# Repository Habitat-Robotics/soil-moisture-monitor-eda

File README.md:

# soil-moisture-monitor-eda
PCB design for soil moisture monitoring circuit
# added circular pcb

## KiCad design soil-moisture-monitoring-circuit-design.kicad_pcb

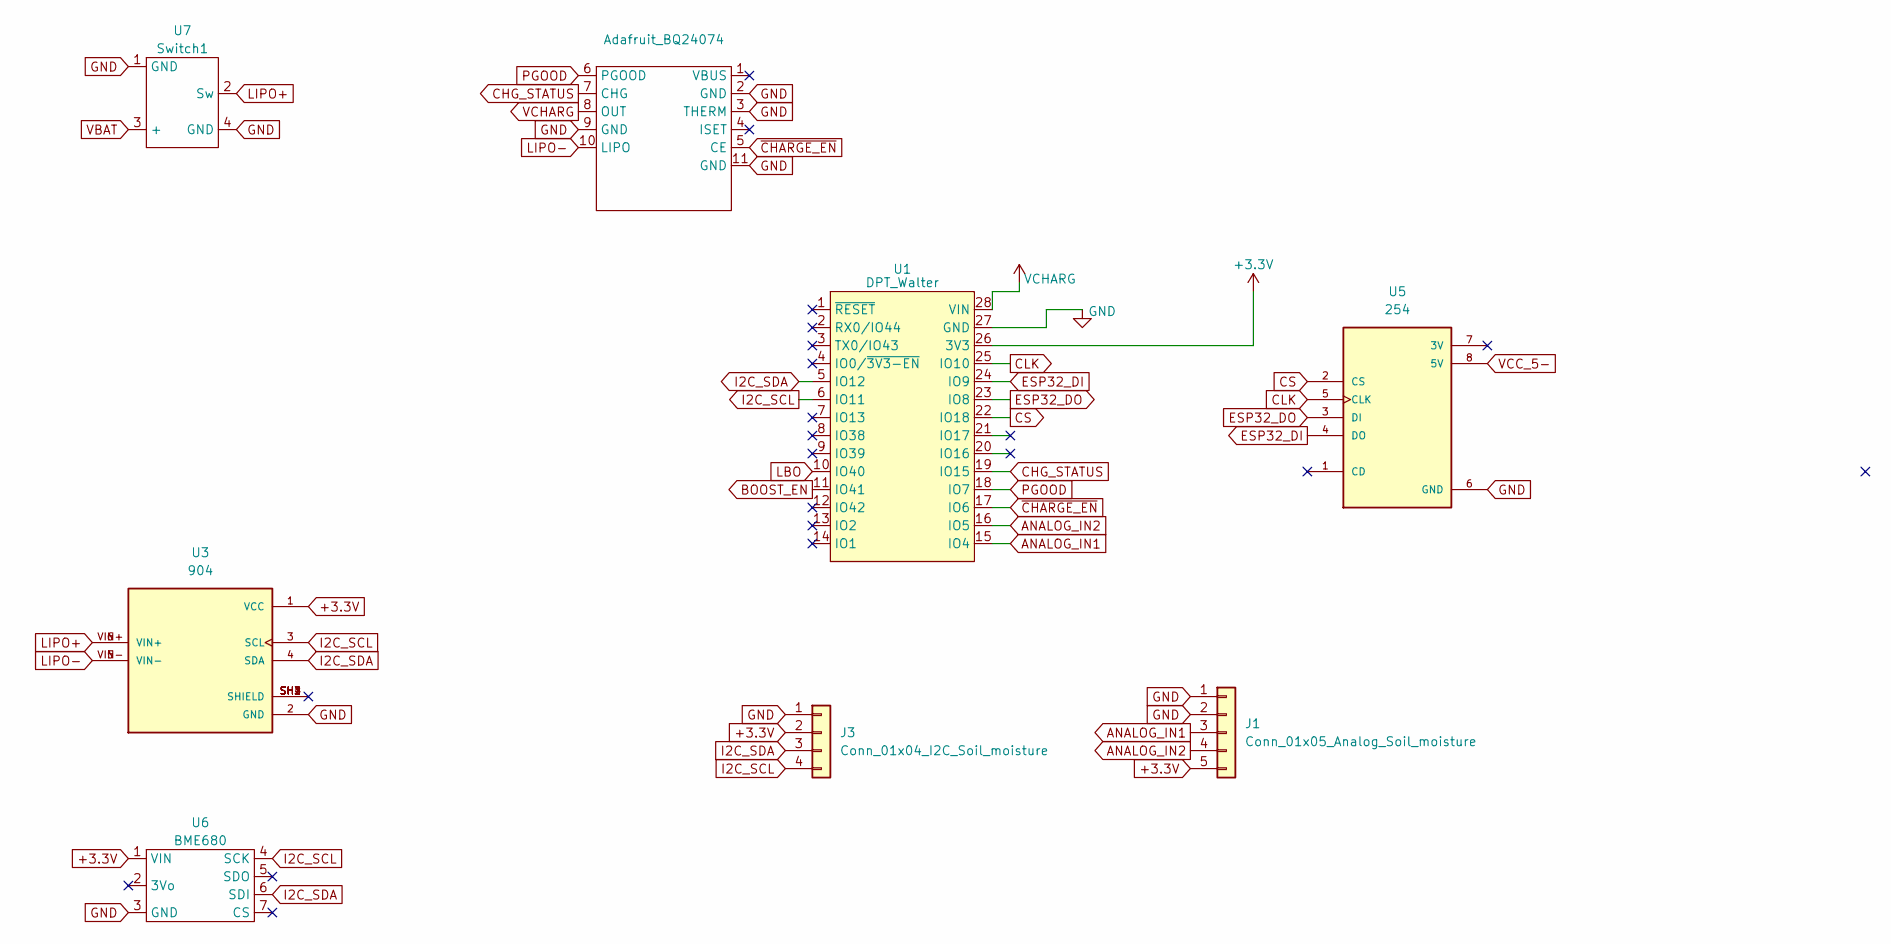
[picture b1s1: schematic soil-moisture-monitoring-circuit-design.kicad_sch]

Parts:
Adafruit_BQ24074: Adafruit_BQ24074
J1: Conn_01x05_Analog_Soil_moisture; PinHeader_1x05_P2.54mm_Vertical
J3: Conn_01x04_I2C_Soil_moisture; PinHeader_1x04_P2.00mm_Vertical
U1: DPT_Walter; walter-solder
U3: 904; MODULE_904; PARTREV C
U5: 254; MODULE_254; PARTREV Jul 31, 2013
U6: BME680; Adafruit_BME680_throughole
U7: Switch1

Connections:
+3.3V: J1.5, J3.2, U1.26 (3V3), U3.1 (VCC), U6.1 (VIN)
ANALOG_IN1: J1.3, U1.15 (IO4)
ANALOG_IN2: J1.4, U1.16 (IO5)
BOOST_EN: U1.11 (IO41)
CHG_STATUS: Adafruit_BQ24074.7 (CHG), U1.19 (IO15)
CLK: U1.25 (IO10), U5.5 (CLK)
CS: U1.22 (IO18), U5.2 (CS)
ESP32_DI: U1.24 (IO9), U5.4 (DO)
ESP32_DO: U1.23 (IO8), U5.3 (DI)
GND: Adafruit_BQ24074.2 (GND), Adafruit_BQ24074.3 (THERM), Adafruit_BQ24074.9 (GND), Adafruit_BQ24074.11 (GND), J1.1, J1.2, J3.1, U1.27 (GND), U3.2 (GND), U5.6 (GND), U6.3 (GND), U7.1 (GND), U7.4 (GND)
I2C_SCL: J3.4, U1.6 (IO11), U3.3 (SCL), U6.4 (SCK)
I2C_SDA: J3.3, U1.5 (IO12), U3.4 (SDA), U6.6 (SDI)
LBO: U1.10 (IO40)
LIPO+: U3.6 (VIN+), U3.VIN+, U7.2 (Sw)
LIPO-: Adafruit_BQ24074.10 (LIPO), U3.5 (VIN-), U3.VIN-
PGOOD: Adafruit_BQ24074.6 (PGOOD), U1.18 (IO7)
VBAT: U7.3 (+)
VCC_5-: U5.8 (5V)
VCHARG: Adafruit_BQ24074.8 (OUT), U1.28 (VIN)
~CHARGE_EN: Adafruit_BQ24074.5 (CE), U1.17 (IO6)

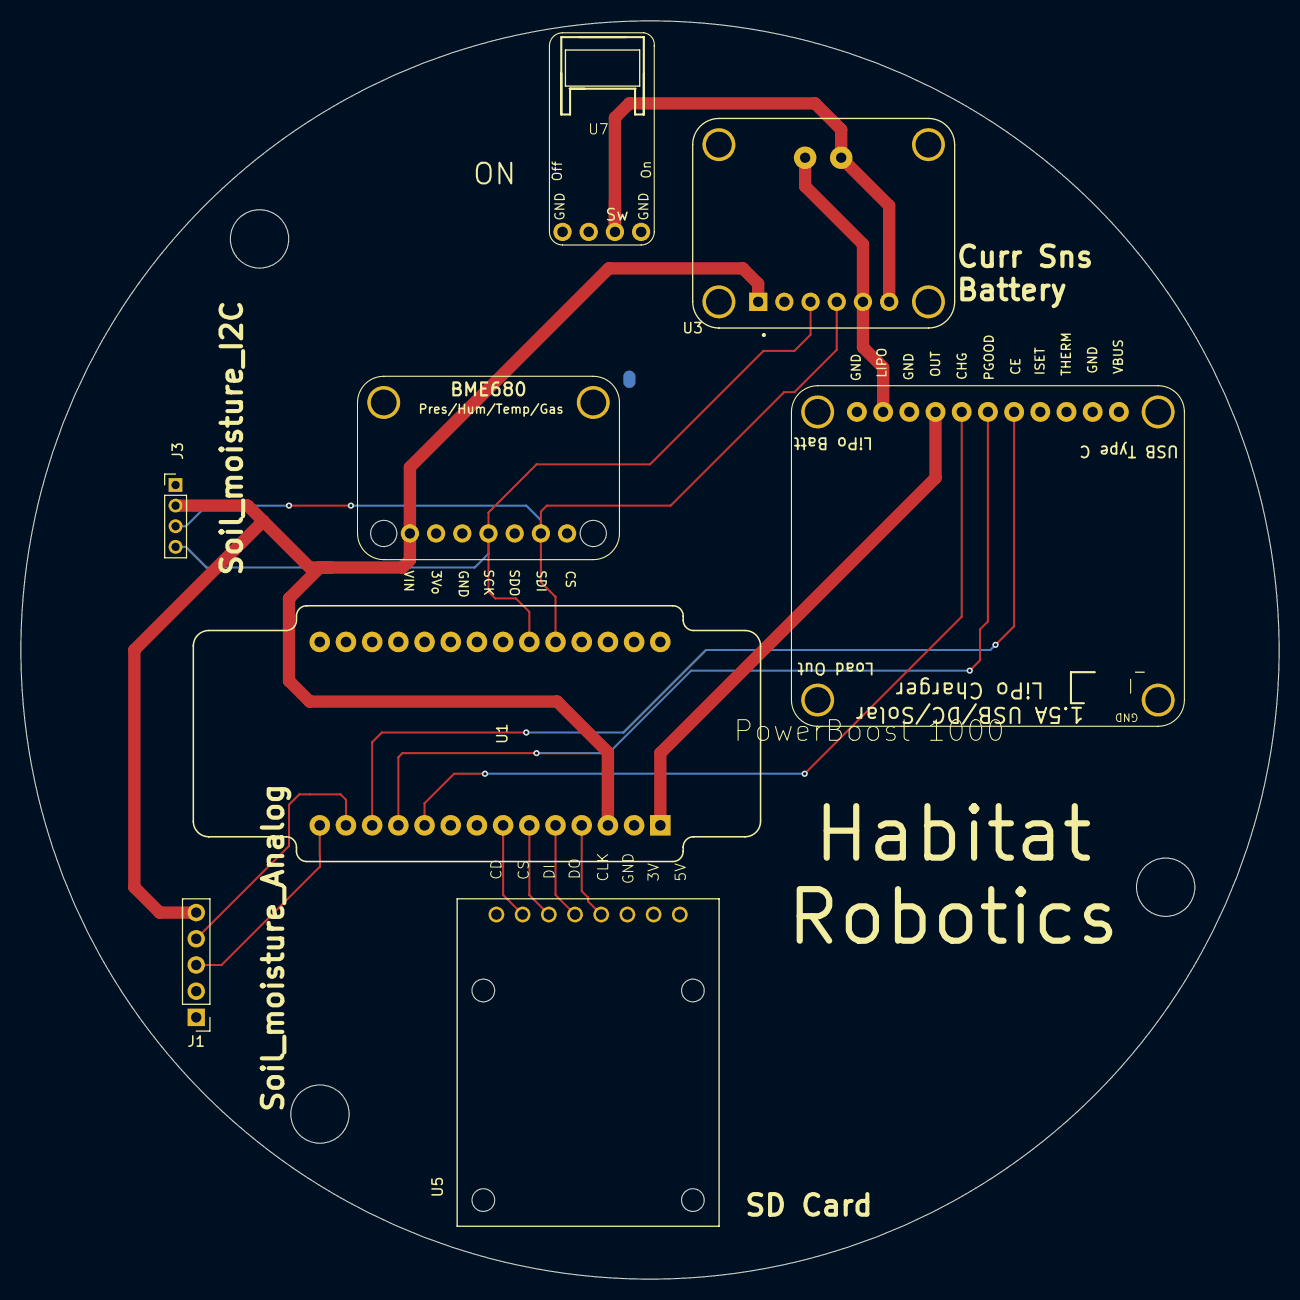
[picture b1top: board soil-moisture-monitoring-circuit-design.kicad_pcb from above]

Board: 2 copper layers, 122.0 x 122.0 mm, 8 parts (0 on the bottom side), 16 nets.

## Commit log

2025-02-02 Initial commit - schematic design
2025-02-02 Initial placement and routing
2025-04-13 updated simplified design from Karun Potty
2025-04-14 outline of 122mm diameter
2025-04-15 added STEP file
2025-04-21 added some comments in readme file
